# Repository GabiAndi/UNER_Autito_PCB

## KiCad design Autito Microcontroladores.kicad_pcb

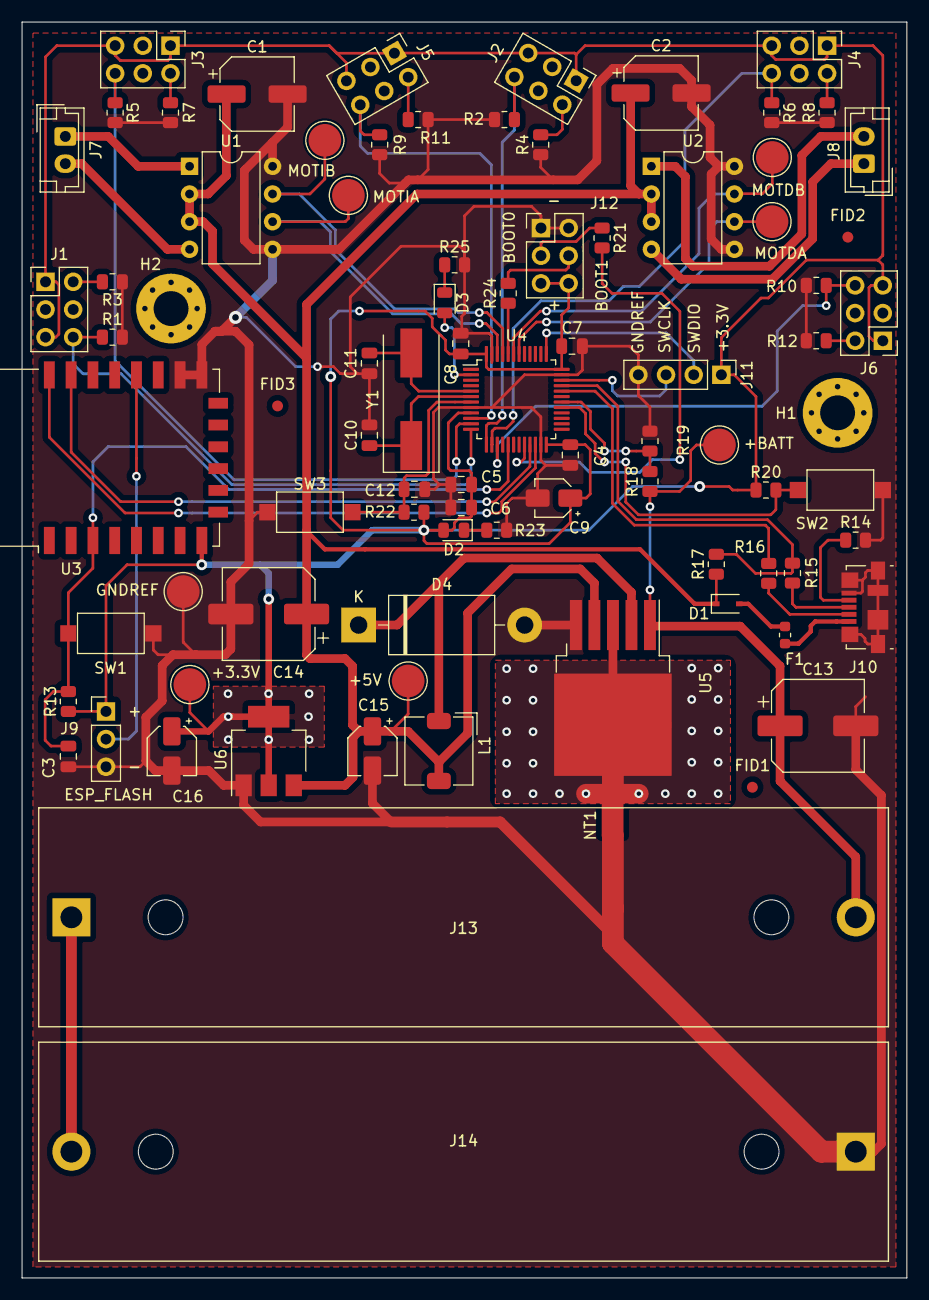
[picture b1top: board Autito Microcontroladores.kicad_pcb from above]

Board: 2 copper layers, 81.2 x 115.3 mm, 85 parts (0 on the bottom side), 52 nets.

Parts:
+3.3V, +5V: TestPoint; TestPoint_Pad_D3.0mm
+BATT: TestPoint; TestPoint_Pad_D3.0mm
C1, C2: 22uF; CP_Elec_6.3x9.9
C3, C4, C5, C6, C7, C8, C12: 100nF; C_0805_2012Metric
C9: 4.7uF; CP_Elec_3x5.4
C10, C11: 20pF; C_0805_2012Metric
C13, C14: 220uF; CP_Elec_8x6.9
C15, C16: 22uF; CP_Elec_4x5.8
D1: BAT60A; D_SOD-323
D2, D3: LED; D_0805_2012Metric
D4: 1N5822; D_DO-201AD_P15.24mm_Horizontal
F1: 500mA; Fuse_0603_1608Metric
FID1, FID2, FID3: Fiducial; Fiducial_1mm_Mask2mm
GNDREF: TestPoint; TestPoint_Pad_D3.0mm
H1, H2: MountingHole; MountingHole_3.2mm_M3_Pad_Via
J1: SENSOR 1; TCRT5000
J2: SENSOR 4; TCRT5000
J3: SENSOR 2; TCRT5000
J4: SENSOR 5; TCRT5000
J5: SENSOR 3; TCRT5000
J6: SENSOR 6; TCRT5000
J7: Motor izquierda; JST_EH_B2B-EH-A_1x02_P2.50mm_Vertical
J8: Motor derecha; JST_EH_B2B-EH-A_1x02_P2.50mm_Vertical
J9: Flash enable; PinHeader_1x03_P2.54mm_Vertical
J10: USB; USB_Micro-B_Molex_47346-0001
J11: SWD; PinHeader_1x04_P2.54mm_Vertical
J12: BOOT MODE; PinHeader_2x03_P2.54mm_Vertical
J13: Batería2; BatteryHolder_MPD_BH-18650-PC2
J14: Bateria1; BatteryHolder_MPD_BH-18650-PC2
L1: 33uH; L_TDK_SLF6045
MOTDA: TestPoint; TestPoint_Pad_D3.0mm
MOTDB: TestPoint; TestPoint_Pad_D3.0mm
MOTIA: TestPoint; TestPoint_Pad_D3.0mm
MOTIB: TestPoint; TestPoint_Pad_D3.0mm
NT1: Net-Tie_2; NetTie-2_SMD_Pad2.0mm
R1, R2, R5, R6, R9, R10: 50k; R_0805_2012Metric
R3, R4, R7, R8, R11, R12: 120R; R_0805_2012Metric
R13, R14, R19, R20, R22: 10k; R_0805_2012Metric
R15, R16: 20R; R_0805_2012Metric
R17: 4.7k; R_0805_2012Metric
R18: 20k; R_0805_2012Metric
R21, R24: 100k; R_0805_2012Metric
R23, R25: 110R; R_0805_2012Metric
SW1, SW3: RESET; SW_SPST_CK_RS282G05A3
SW2: PID Init; SW_SPST_CK_RS282G05A3
U1, U2: L9110; DIP-8_W7.62mm
U3: ESP-12F; ESP-12E
U4: STM32F103C8Tx; LQFP-48_7x7mm_P0.5mm
U5: LM2596S-5; TO-263-5_TabPin3
U6: AMS1117-3.3; SOT-223-3_TabPin2
Y1: 8MHz; Crystal_SMD_HC49-SD

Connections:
+3V3: +3.3V.1, C4.1, C5.1, C6.1, C7.1, C8.1, C9.1, C16.1, D2.2, J1.1, J1.5, J2.1, J2.5, J3.1, J3.5, J4.1, J4.5, J5.1, J5.5, J6.1, J6.5, J9.1, J11.1, J12.5, J12.6, R13.1, R20.1, R22.1, U3.8, U4.9, U4.24, U4.36, U4.48, U6.2
+5V: +5V.1, C1.1, C2.1, C14.1, C15.1, D1.1, L1.2, R17.2, U1.2, U1.3, U2.2, U2.3, U5.4, U6.3
+BATT: +BATT.1, C13.1, J13.2, R18.1, U5.1
/Microcontrolador/BOOT0: R24.1, U4.44
/Microcontrolador/BOOT1: R21.2, U4.20
/Microcontrolador/OSC_IN: C11.1, U4.5, Y1.2
/Microcontrolador/OSC_OUT: C10.1, U4.6, Y1.1
/Microcontrolador/PID_INIT: R20.2, SW2.2, U4.29
/Microcontrolador/RST: C12.1, R22.2, SW3.2, U4.7
/Microcontrolador/STATUS_LED: D3.2, U4.2
/Microcontrolador/SWCLK: J11.3, U4.34
/Microcontrolador/SWDIO: J11.2, U4.37
/Microcontrolador/USBB_N: J10.2, R16.2
/Microcontrolador/USBB_P: J10.3, R15.2
/Microcontrolador/USBD_N: R16.1, U4.32
/Microcontrolador/USBD_P: R15.1, R17.1, U4.33
/Microcontrolador/V_BAT: R18.2, R19.1, U4.30
/WiFi/ESP_FLASH_ENABLE: J9.2, U3.18
ESP_SOFT_RST: C3.1, R13.2, SW1.2, U3.3, U4.17
GND1: NT1.2, U5.3
GNDREF: C1.2, C2.2, C3.2, C4.2, C5.2, C6.2, C7.2, C8.2, C9.2, C10.2, C11.2, C12.2, C13.2, C14.2, C15.2, C16.2, D4.2, GNDREF.1, J9.3, J10.5, J10.6, J11.4, J12.1, J12.2, J14.1, NT1.1, R1.2, R2.2, R3.1, R4.1, R5.2, R6.2, R7.1, R8.1, R9.2, R10.2, R11.1, R12.1, R14.2, R19.2, R23.2, R25.2, SW1.1, SW2.1, SW3.1, U1.5, U1.8, U2.5, U2.8, U3.15, U3.16, U4.8, U4.23, U4.35, U4.47, U5.5, U6.1
MOTDA: MOTDA.1, U2.6, U4.42
MOTDB: MOTDB.1, U2.7, U4.43
MOTIA: MOTIA.1, U1.6, U4.46
MOTIB: MOTIB.1, U1.7, U4.45
unnamed: D1.2, F1.1
unnamed: D2.1, R23.1
unnamed: D3.1, R25.1
unnamed: D4.1, L1.1, U5.2
unnamed: F1.2, J10.1
unnamed: J1.2, R3.2
unnamed: J2.2, R4.2
unnamed: J3.2, R7.2
unnamed: J4.2, R8.2
unnamed: J5.2, R11.2
unnamed: J6.2, R12.2
unnamed: J7.1, U1.1
unnamed: J7.2, U1.4
unnamed: J8.1, U2.4
unnamed: J8.2, U2.1
unnamed: J10.4, R14.1
unnamed: J12.3, R21.1
unnamed: J12.4, R24.2
unnamed: J13.1, J14.2
SENSOR1: J1.6, R1.1, U4.12
SENSOR2: J3.6, R5.1, U4.11
SENSOR3: J5.6, R9.1, U4.10
SENSOR4: J2.6, R2.1, U4.13
SENSOR5: J4.6, R6.1, U4.14
SENSOR6: J6.6, R10.1, U4.15
UART_RX: U3.22, U4.22
UART_TX: U3.21, U4.21

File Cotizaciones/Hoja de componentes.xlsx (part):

|  |  | Autito Microcontroladores
 |  |  | Gabriel Andrés Aguirre
Componente | Referencia | Valor | Footprint | Link | Precio unidad | Precio unidad | Cantidad | Precio | Fabricante | N.º Fabricante | Mouser N.º
Resistencias de 50k | R10, R6, R2, R9, R5, R1 | 50k | Resistor_SMD:R_0805_2012Metric | https://ar.mouser.com/ProductDetail/KOA-Speer/RN73H2ATTD1503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 | 71.32 | 0.509428571428571 | 6 | 3.05657142857143 | KOA Speer | RN73H2ATTD1503B25 | 660-RN73H2ATD1503B25
Sensores infrarojos | J6, J5, J2, J4, J1, J3 | SENSOR | Mis_componentes:TCRT5000 | https://ar.mouser.com/ProductDetail/Vishay-Semiconductors/TC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 | 121.54 | 0.868142857142857 | 6 | 5.20885714285714 | Vishay Semiconductors | TCRT5000 | 782-TCRT5000
Resistencia de 120R | R12, R8, R4, R11, R7, R3 | 120R | Resistor_SMD:R_0805_2012Metric | https://ar.mouser.com/ProductDetail/Panasonic/ERA-6VEB1200V?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 | 70.32 | 0.502285714285714 | 6 | 3.01371428571429 | Panasonic | ERA-6VEB1200V | 667-ERA-6VEB1200V
Puente H | U1, U2 | L9110 | Package_DIP:DIP-8_W7.62mm | https://ar.mouser.com/ProductDetail/Adafruit/4489?qs=%2Fha2p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 | 150.68 | 1.07628571428571 | 2 | 2.15257142857143 | Adafruit | 4489 | 485-4489
Capacitor de 22uF | C1, C2, C16, C15 | 22uF | Capacitor_SMD:CP_Elec_6.3x9.9 | https://ar.mouser.com/ProductDetail/Panasonic/EEE-FN1C220R?q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 | 32.14 | 0.229571428571429 | 4 | 0.918285714285714 | Panasonic | EEE-FN1C220R | 667-EEE-FN1C220R
Conector para motores | J7, J8 | Motor | Connector_JST:JST_EH_B2B-EH-A_1x02_P2.50mm_Vertical | https://ar.mouser.com/ProductDetail/JST-Automotive/S06B-AIT2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 | 80.36 | 0.574 | 2 | 1.148 | JST Automotive | S06B-AIT2-1AK | 306-S06B-AIT2-1AK
Modulo WiFi ESP8266 | U3 | ESP-12F | RF_Module:ESP-12E | https://ar.mouser.com/ProductDetail/Adafruit/2491?qs=N%2F3wi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 | 698.13 | 4.98664285714286 | 1 | 4.98664285714286 | Adafruit | 2491 | 485-2491
Capacitor de 100nF | C3, C4, C6, C5, C8, C12, C7 | 100nF | Capacitor_SMD:C_0805_2012Metric | https://ar.mouser.com/ProductDetail/KEMET/C0805X104M5RACTU?q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 | 52.23 | 0.373071428571429 | 7 | 2.6115 | KEMET | C0805X104M5RACTU | 80-C0805X104M5RACTU
Capacitor de 20pF | C10, C11 | 20pF | Capacitor_SMD:C_0805_2012Metric | https://ar.mouser.com/ProductDetail/AVX/08055A200F4T2A?qs=XL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 | 49.22 | 0.351571428571429 | 2 | 0.703142857142857 | AVX | 08055A200F4T2A | 581-08055A200F4T2A
Boton pulsador pequeño | SW1, SW2, SW3 | Button | Button_Switch_SMD:SW_SPST_CK_RS282G05A3 | https://ar.mouser.com/ProductDetail/?qs=vLWxofP3U2xHB0Q2opWS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 | 10.05 | 0.0717857142857143 | 3 | 0.215357142857143 | C&K | PTS636 SL43 LFS | 611-PTS636SL43LFS
Resistencia de 10k | R13, R22, R14, R19, R20 | 10k | Resistor_SMD:R_0805_2012Metric | https://ar.mouser.com/ProductDetail/Vishay-Dale/CRCW080510K0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 | 10.05 | 0.0717857142857143 | 5 | 0.358928571428571 | Vishay / Dale | CRCW080510K0FKEAC | 71-CRCW080510K0FKEAC
PinHeader 01x03 | J9 | Flash enable | Connector_PinHeader_2.54mm:PinHeader_1x03_P2.54mm_Vertical | https://ar.mouser.com/ProductDetail/Digilent/240-004?qs=s%2F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 | 149.67 | 1.06907142857143 | 1 | 1.06907142857143 | Digilent | 240-004 | 424-6-PIN-HEADER
Cristal de 8MHz | Y1 | 8MHz | Crystal:Crystal_SMD_HC49-SD | https://ar.mouser.com/ProductDetail/ECS/ECS-80-20-5PVX-TR?qs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 | 156.7 | 1.11928571428571 | 1 | 1.11928571428571 | ECS | ECS-80-20-5PVX-TR | 520-ECS-80-20-5PVX
Resistencia de 100k | R24, R21 | 100k | Resistor_SMD:R_0805_2012Metric | https://ar.mouser.com/ProductDetail/Vishay-Dale/CRCW0805100K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 | 10.05 | 0.0717857142857143 | 2 | 0.143571428571429 | Vishay / Dale | CRCW0805100KJNEAC | 71-CRCW0805100KJNEAC
PinHeader 02x03 | J12 | BOOT MODE | Connector_PinHeader_2.54mm:PinHeader_2x03_P2.54mm_Vertical | https://ar.mouser.com/ProductDetail/Digilent/240-062?qs=s%2F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 | 210.95 | 1.50678571428571 | 1 | 1.50678571428571 | Digilent | 240-062 | 424-2X6-PIN-HEADER
PinHeader 01x04 | J11 | SWD | Connector_PinHeader_2.54mm:PinHeader_1x04_P2.54mm_Vertical | https://ar.mouser.com/ProductDetail/Digilent/240-004?qs=s%2F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 | 149.67 | 1.06907142857143 | 1 | 1.06907142857143 | Digilent | 240-004 | 424-6-PIN-HEADER
Resistencia de 20R | R15, R16 | 20R | Resistor_SMD:R_0805_2012Metric | https://ar.mouser.com/ProductDetail/Vishay-Dale/RCS080520R0F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 | 25.11 | 0.179357142857143 | 2 | 0.358714285714286 | Vishay / Dale | RCS080520R0FKEA | 71-RCS080520R0FKEA
Conector micro USB hermbra | J10 | USB | Connector_USB:USB_Micro-B_Molex_47346-0001 | https://ar.mouser.com/ProductDetail/CUI-Devices/UJ2-MIBH-G-S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 | 45.2 | 0.322857142857143 | 1 | 0.322857142857143 | CUI Devices | UJ2-MIBH-G-SMT-TR | 490-UJ2-MIBH-G-SMTTR
Resistencia de 4,7k | R17 | 4.7k | Resistor_SMD:R_0805_2012Metric | https://ar.mouser.com/ProductDetail/Vishay-Dale/CRCW08054K70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 | 10.05 | 0.0717857142857143 | 1 | 0.0717857142857143 | Vishay / Dale | CRCW08054K70JNEA | 71-CRCW0805J-4.7K-E3
Resistencia de 20k | R18 | 20k | Resistor_SMD:R_0805_2012Metric | https://ar.mouser.com/ProductDetail/Vishay-Dale/CRCW080520K0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 | 10.05 | 0.0717857142857143 | 1 | 0.0717857142857143 | Vishay / Dale | CRCW080520K0FKEAC | 71-CRCW080520K0FKEAC
Capacitor de 4,7uF | C9 | 4.7uF | Capacitor_SMD:CP_Elec_3x5.4 | https://ar.mouser.com/ProductDetail/Wurth-Elektronik/8650904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 | 30.14 | 0.215285714285714 | 1 | 0.215285714285714 | Wurth Elektronik | 865090468011 | 710-865090468011
LED verde | D3 | LED | Diode_SMD:D_0805_2012Metric | https://ar.mouser.com/ProductDetail/Dialight/598-8C80-102F?q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 | 39.18 | 0.279857142857143 | 1 | 0.279857142857143 | Dialight | 598-8C80-102F | 645-598-8C80-102F
LED naranja | D2 | LED | Diode_SMD:D_0805_2012Metric | https://ar.mouser.com/ProductDetail/Dialight/598-8C30-102F?q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 | 34.15 | 0.243928571428571 | 1 | 0.243928571428571 | Dialight | 598-8C30-102F | 645-598-8C30-102F
Resistencia de 10R | R25, R23 | 110R | Resistor_SMD:R_0805_2012Metric | https://ar.mouser.com/ProductDetail/Vishay-Dale/CRCW0805110R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 | 16.07 | 0.114785714285714 | 2 | 0.229571428571429 | Vishay / Dale | CRCW0805110RFKEAC | 71-CRCW0805110RFKEAC
Fusible rearmable de 500mA | F1 | 500mA | Fuse:Fuse_0603_1608Metric | https://ar.mouser.com/ProductDetail/Littelfuse/1812L050-60MR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 | 92.41 | 0.660071428571429 | 1 | 0.660071428571429 | Littelfuse | 1812L050/60MR | 576-1812L050/60MR
Diodo de baja caida | D1 | BAT60A | Diode_SMD:D_SOD-323 | https://ar.mouser.com/ProductDetail/Infineon-Technologies/BA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 | 45.2 | 0.322857142857143 | 1 | 0.322857142857143 | Infineon Technologies | BAT 60A E6327 | 726-BAT60AE6327
STM microcontrolador | U4 | STM32F103C8Tx | Package_QFP:LQFP-48_7x7mm_P0.5mm | https://ar.mouser.com/ProductDetail/STMicroelectronics/STM32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 | 571.56 | 4.08257142857143 | 1 | 4.08257142857143 | STMicroelectronics | STM32F103CBT6 | 511-STM32F103CBT6
Conversor DC-DC a 5V | U5 | LM2596S-5 | Package_TO_SOT_SMD:TO-263-5_TabPin3 | https://ar.mouser.com/ProductDetail/Texas-Instruments/LM2596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 | 609.73 | 4.35521428571429 | 1 | 4.35521428571429 | Texas Instruments | LM2596S-5.0/NOPB | 926-LM2596S-5.0/NOPB
Capacitor de 220uF | C14, C13 | 220uF | Capacitor_SMD:CP_Elec_8x6.9 | https://ar.mouser.com/ProductDetail/Nichicon/PCH1C221MCL1GS?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 | 212.95 | 1.52107142857143 | 2 | 3.04214285714286 | Nichicon | PCH1C221MCL1GS | 647-PCH1C221MCL1GS
Inductor de 33uH | L1 | 33uH | Inductor_SMD:L_TDK_SLF6045 | https://ar.mouser.com/ProductDetail/Taiyo-Yuden/NS10145T330M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 | 177.8 | 1.27 | 1 | 1.27 | Taiyo Yuden | NS10145T330MNV8 | 963-NS10145T330MNV8
Conversor lineal 5V a 3,3V | U6 | AMS1117-3.3 | Package_TO_SOT_SMD:SOT-223-3_TabPin2 | https://ar.mouser.com/ProductDetail/Texas-Instruments/LM1117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 | 66 | 0.471428571428571 | 1 | 0.471428571428571 | Texas Instruments | LM1117MPX-3.3/NOPB | 926-LM1117MPX3.3NOPB
Diodo Schotky | D4 | 1N5822 | Diode_THT:D_DO-201AD_P15.24mm_Horizontal | https://ar.mouser.com/ProductDetail/STMicroelectronics/1N582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 | 115.52 | 0.825142857142857 | 1 | 0.825142857142857 | STMicroelectronics | 1N5822 | 511-1N5822
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
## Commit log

2021-03-20 Diseño completo
    Esquemático y PCB completo
2021-03-22 Planos de tierra
    Terminado el PCB con sujeciones
2021-04-09 Placa terminada
2021-04-12 Entrega de PCB
2021-04-20 Entrega
